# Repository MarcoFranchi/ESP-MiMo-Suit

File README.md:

# ESP-MiMo-Suit
Lighting MIcroMOdule for Home Automation based on ESP8266 WiFi Module
The MiMo suit is currently composed of three modules:
MiMo-Light (control Light)
MiMo-Button (two buttons)
MiMo-3Realy (three relays)

Common feature:

Compatible with existing electrical plant
minimal changes to the electrical system are necessary, the modules can be installed in the wall box, it is not necessary to install new wires, they can work with pushbuttons or standard switches
Safety and super reliable Buttom/Switch control.
no restriction on the length of the connection wires of the Buttons/Switch (the botton/switch are controlled with the AC Voltage and optoisolated versus the module logic)
Solid State Relay
Optoisolated enad zero cross detect relay for safety and no mechanical and electrical noise
Compatible with ESP Firmware
Espurna, ESP Easy, Tasmota and all firmware for ESP can be used for control

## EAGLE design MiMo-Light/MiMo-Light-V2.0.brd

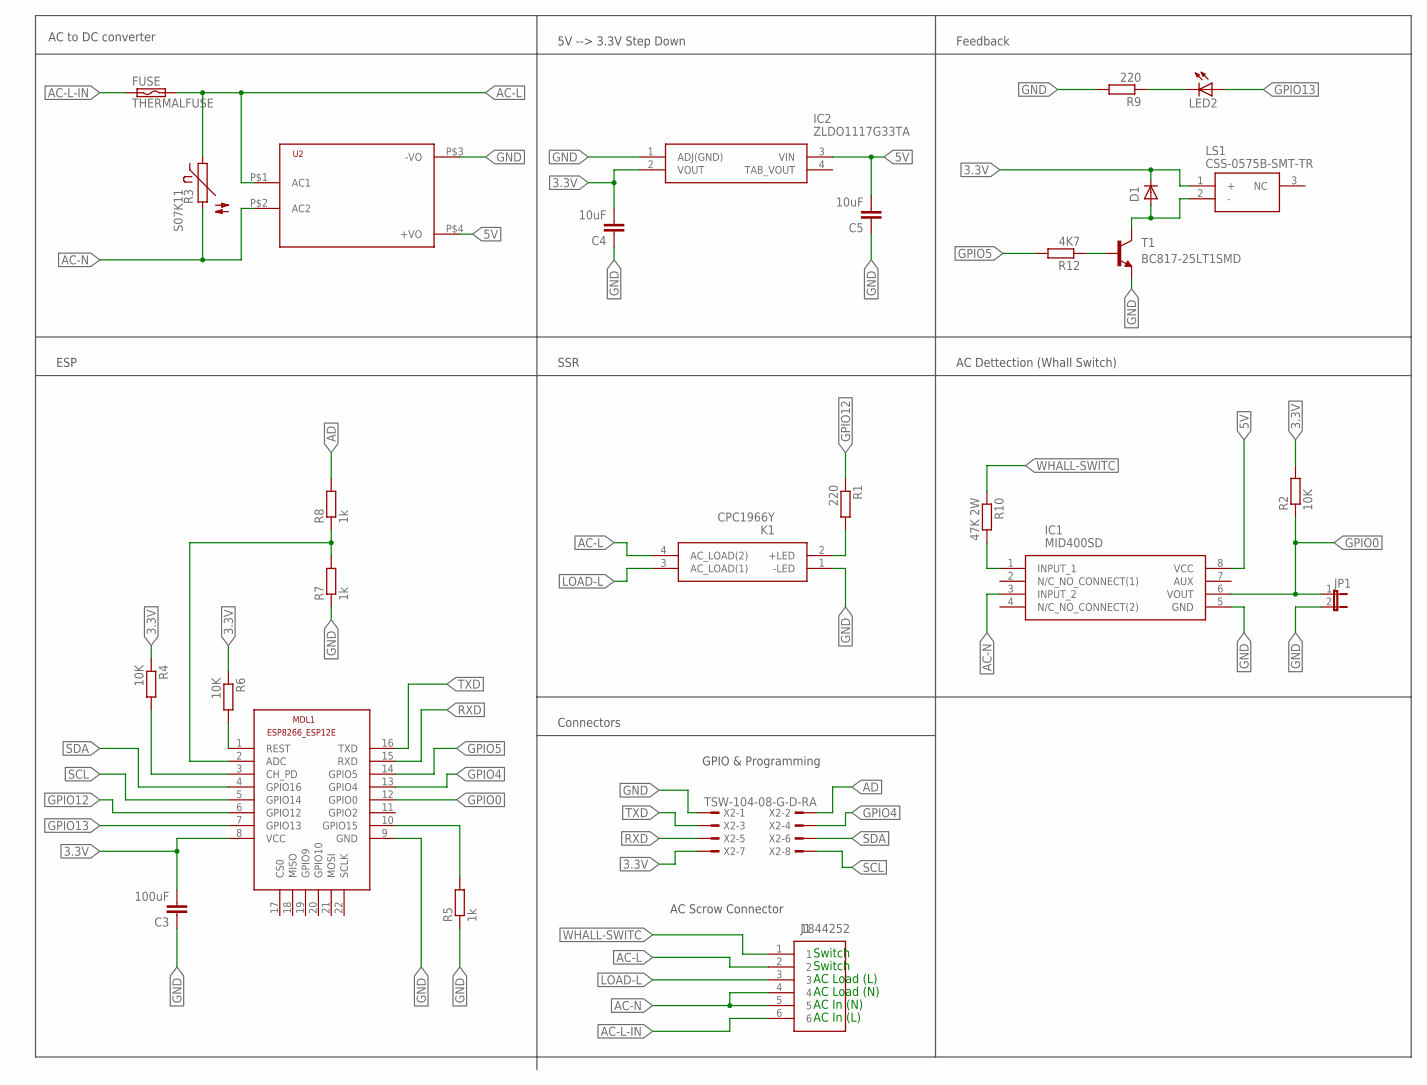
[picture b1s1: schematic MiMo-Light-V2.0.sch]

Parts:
C3: 100uF; 1210
C4, C5: 10uF; 1206
D1: DIODE-MINIMELF; MINIMELF
FUSE: THERMALFUSE; TE5
IC1: MID400SD; SOP254P1030X508-8N
IC2: ZLDO1117G33TA; SOT230P700X180-4N
J1: 1844252; SHDR6W100P0X350_1X6_2240X920X7
JP1: JP1E; JP1
K1: CPC1966Y
LED2: LEDCHIPLED_1206; CHIPLED_1206
LS1: CSS-0575B-SMT-TR
MDL1: ESP8266-12EESP8266-ESP12E; ESP8266-ESP12E
R1, R9: 220; R1206
R2, R4, R6: 10K; R1206
R3: S07K11
R5, R7, R8: 1k; R1206
R10: 47K 2W; R2512
R12: 4K7; R1206
T1: BC817-25LT1SMD; SOT23-BEC
U2: HLK-PM013W; HLK-PM01
X2: TSW-104-08-G-D-RA

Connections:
3.3V: C3.2, C4.2, D1.C, IC2.2 (VOUT), LS1.1 (+), MDL1.8 (VCC), R2.2, R4.1, R6.1, X2.7
5V: C5.2, IC1.8 (VCC), IC2.3 (VIN), U2.P$4 (+VO)
AC-DETECT: IC1.1 (INPUT_1), R10.2
AC-L: FUSE.2, J1.2, K1.4 (AC_LOAD(2)), R3.1, U2.P$1 (AC1)
AC-L-IN: FUSE.1, J1.6
AC-N: IC1.3 (INPUT_2), J1.4, J1.5, R3.2, U2.P$2 (AC2)
AD: R8.2, X2.2
ADC: MDL1.2 (ADC), R7.2, R8.1
GND: C3.1, C4.1, C5.1, IC1.5 (GND), IC2.1 (ADJ(GND)), JP1.2, K1.1 (-LED), MDL1.9 (GND), R5.1, R7.1, R9.2, T1.E, U2.P$3 (-VO), X2.1
GPIO0: IC1.6 (VOUT), JP1.1, MDL1.12 (GPIO0), R2.1
GPIO4: MDL1.13 (GPIO4), X2.4
GPIO5: MDL1.14 (GPIO5), R12.2
GPIO12: MDL1.6 (GPIO12), R1.1
GPIO13: LED2.A, MDL1.7 (GPIO13)
LOAD-L: J1.3, K1.3 (AC_LOAD(1))
unnamed: LED2.C, R9.1
unnamed: K1.2 (+LED), R1.2
unnamed: D1.A, LS1.2 (-), T1.C
unnamed: MDL1.3 (CH_PD), R4.2
unnamed: R12.1, T1.B
unnamed: MDL1.10 (GPIO15), R5.2
unnamed: MDL1.1 (REST), R6.2
RXD: MDL1.15 (RXD), X2.5
SCL: MDL1.5 (GPIO14), X2.8
SDA: MDL1.4 (GPIO16), X2.6
TXD: MDL1.16 (TXD), X2.3
WHALL-SWITC: J1.1, R10.1

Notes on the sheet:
SSR
AC to DC converter
5V --> 3.3V Step Down
Feedback
AC Dettection (Whall Switch)
Connectors
GPIO & Programming
AC Scrow Connector
Switch
AC Load (L)
AC Load (N)
AC In (N)
AC In (L)
ESP

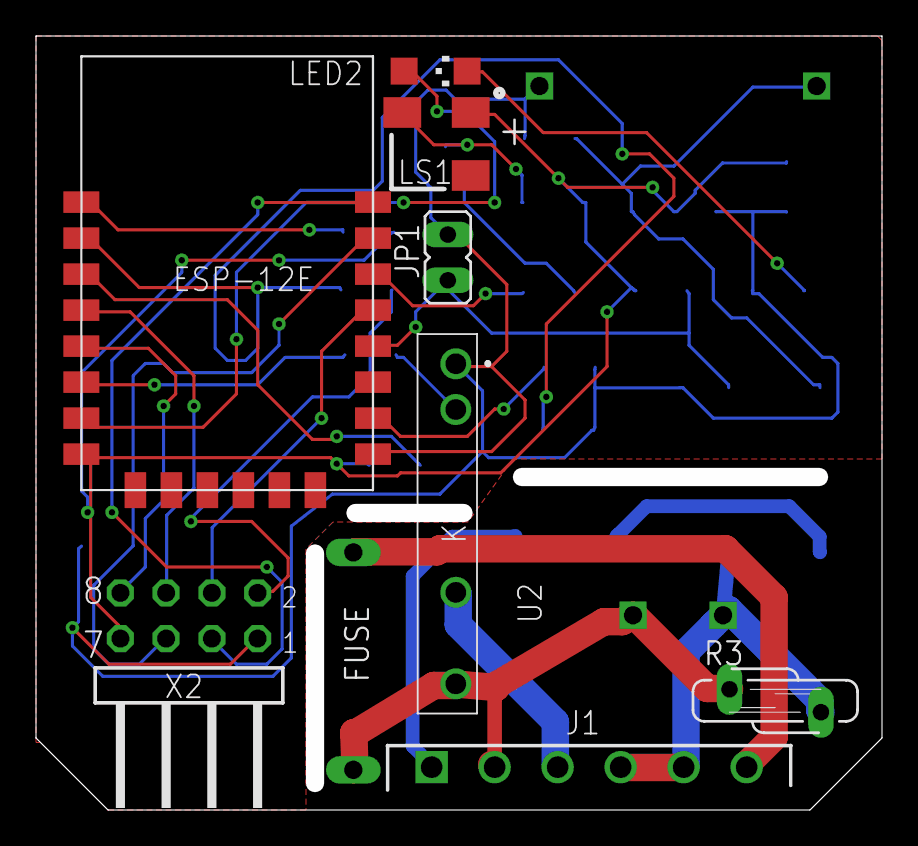
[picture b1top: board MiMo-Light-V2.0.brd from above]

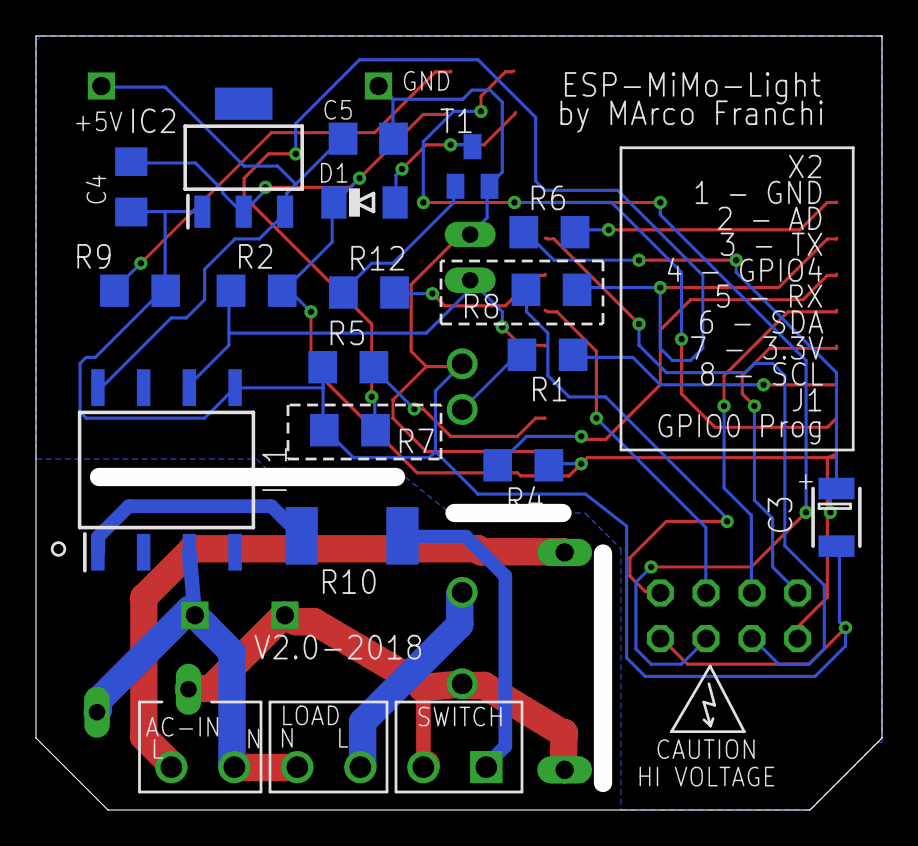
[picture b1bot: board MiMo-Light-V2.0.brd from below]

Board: 2 copper layers, 46.0 x 42.0 mm, 27 parts (17 on the bottom side), 27 nets.

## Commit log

2018-08-24 Create test

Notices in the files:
parts and their libraries:
SparkFun-Capacitors: Licensing: Creative Commons ShareAlike 4.0 International - https://creativecommons.org/licenses/by-sa/4.0
